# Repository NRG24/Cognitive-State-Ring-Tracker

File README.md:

# NERVA Ring

An open-source, sensor-packed smart ring designed to monitor cognitive health and autonomic nervous system metrics rather than traditional fitness tracking.

## Project Overview

The NERVA Ring shifts the focus of wearable technology away from step-counting and workouts toward real-time mental well-being. By embedding precise biosensors into a compact, flexible PCB form factor, the device continuously captures physiological indicators tied directly to stress, mental fatigue, and psychological arousal.

## Core Features

* **Cognitive Focus:** Tailored strictly for mental wellness monitoring rather than physical fitness or gym tracking.
* **Reviewed Hardware Design:** The v1 circuitry was modeled and validated in LT-Spice; the v2 netlist has been reviewed pin-by-pin against every device datasheet. No v2 board has been built or bench-validated yet.
* **Ultra-Compact Layout:** All hardware components optimized to fit onto a highly constrained, circular flex PCB architecture.
* **Wireless Telemetry:** Real-time, low-latency data streaming to mobile devices using Bluetooth Low Energy (BLE).
* **Intelligent Software Pipeline:** Dynamic in-app data filtering to remove motion artifacts and anomalies, powering a custom algorithm that delivers a "Cognitive Score" out of 100 alongside meaningful behavioral insights.

## Hardware Architecture

The current board is **NERVA Ring v2**, a complete part change from v1 — the MCU, both sensors, the op-amp, and the entire power path were replaced. Everything under `hardware/` and `firmware/` in this repo still describes the v1 board; see [Board Revisions](#board-revisions).

### Core components

| Role | Part | I²C address (7-bit) |
|------|------|---------------------|
| MCU / BLE | u-blox ANNA-B402-00B (nRF52833) | — |
| PPG (HR / SpO2) | MAXM86161 | `0x62` (`0xC4`/`0xC5` 8-bit) |
| IMU + die temperature | ST LSM6DSV | `0x6B` — SA0 tied to 1V8 |
| PMIC / charger / fuel gauge | TI BQ25120A | `0x6A` (fixed) |
| GSR analog front end | TI OPA2333 (dual op-amp) | — |
| LED boost converter | TI TPS61240 (fixed 5 V) | — |

All three I²C devices share a single bus. The IMU sits at **`0x6B`, not the ST default `0x6A`**: SA0 was originally grounded, which collided with the BQ25120A's fixed `0x6A`, so it was moved to the 1V8 rail.

### Pin map

**ANNA-B402 module pin numbers are not nRF GPIO numbers.** The `Pxx.yy` column is what firmware addresses.

There is **no UART and no USB** on this board — SWD is the only wired interface, so logging has to go over RTT rather than a serial port.

Because XL1/XL2 are grounded, the low-frequency clock has to come from the internal RC oscillator. There is no crystal to select.

### Power architecture

* **BQ25120A** is charger, buck regulator, and fuel gauge in one part. It supplies the SYS rail feeding the ANNA module, both sensors, and the analog front end. There is no separate LDO and no 3.3 V rail — the 3V3 rail was deleted, nothing uses it, and the PMIC's load switch / LDO output stays off (`LSCTRL`, ball E3, is tied to GND).
* **SYS runs at 1.9 V, not the 1.8 V default.** The default's −2.5 % corner is 1.755 V, which is below the OPA2333's 1.800 V minimum supply and only 55 mV above the ANNA's 1.70 V brown-out threshold. 1.9 V clears both, and costs nothing in GSR accuracy because the measurement is ratiometric — the rail cancels out.
* **The TS (thermistor) pin, ball C3, is physically unroutable on this layout and floats.** With TS sensing active the charger faults and delivers no current, so `TS_EN` has to be cleared before the cell will charge at all.
* Disabling TS also removes JEITA over-temperature protection from a lithium cell worn against skin, so charge-temperature limiting has to be reimplemented against the LSM6DSV die temperature and applied through the PMIC's `CE` bit.
* **Battery percentage comes from the BQ25120A's VBMON.** The v1 board had no fuel gauge at all.
* **TPS61240** generates the fixed 5 V VLED rail for the PPG, gated by `BOOST_EN`. It exists because of the green LED: VF is 3.0–3.8 V, against 2.1–2.5 V for red and 1.6–1.9 V for IR.
* Battery capacity (mAh) is still an open decision — it sets the fast-charge current and any honest runtime estimate.

### GSR front end

* Excitation is gated by `GSR_PWR` (P0.11, high drive) so the analog section can be powered down between samples, saving roughly 37 µA.
* Output lands on **AIN1 (P0.03)**. The SAADC is configured **reference VDD/4, gain 1/4**, so full scale equals VDD and the reading is ratiometric against the same rail that drives the excitation — supply drift cancels. The internal 0.6 V reference breaks that property.
* **40 µs acquisition time** is required by the 100 kΩ source impedance of R6.
* The C10/R6 filter has a ~100 ms time constant; allow ~300 ms after powering the front end before the first valid sample.
* Sampling must stay at **≥10 Hz** — skin-conductance responses peak ~1.4 s after onset, which is ~14 samples across the rise at 10 Hz but only ~3 at 2 Hz.
* Nominal conversion, 12-bit (0–4095): `G[µS] ≈ code × 0.009692 − 10.989`. Derived from nominal resistor values, so it needs trimming against a known resistance.

### PPG front end

* The MAXM86161 is powered **entirely from the 5 V VLED rail**. It is single-supply with an internal LDO, so taking `BOOST_EN` low unpowers the part completely and resets every register — a full re-init is required on each duty cycle.
* **Its interrupt pin is deliberately left unconnected**; the FIFO has to be polled.
* The I²C bus runs at 1.8 V and the MAXM86161 needs VIH ≥ 1.4 V, so no level shifter is required despite the 5 V VLED.
* **LED current range is a power-path constraint.** At the 124 mA range the boost pulls ~186 mA from the cell; on a small ring LiPo (~3 Ω internal resistance) that is ~560 mV of droop and starts crowding the BQ25120A's UVLO. The 31 mA range draws ~45 mA, about 135 mV of droop.

### IMU

* LSM6DSV at `0x6B`, with INT1 wired to P0.16.
* It is **not** an LSM6DS3 — different `WHO_AM_I` and different ODR / full-scale register encodings, so v1 register values do not carry the same meaning.
* Embedded temperature sensor at `OUT_TEMP_L/H` (0x20/0x21), 256 LSB/°C with 0 LSB = 25 °C. This is the die temperature used for the software charge-temperature limiting described above.

```
NERVA_Ring/
├── app/                        # Flutter mobile app ("GSR Streamer")
│   ├── lib/
│   │   ├── main.dart           # App entry point
│   │   ├── ble_service.dart    # BLE communication layer
│   │   ├── cognitive_scorer.dart
│   │   ├── gsr_analyzer.dart
│   │   ├── models/             # Data models
│   │   ├── screens/            # UI screens
│   │   ├── services/           # Business logic services
│   │   └── widgets/            # Reusable UI components
│   └── pubspec.yaml
├── firmware/                   # Arduino firmware sketches
│   ├── gsr_heart_ble/          # Main firmware + docs
│   │   ├── gsr_heart_ble.ino   # BLE biometric streaming (XIAO prototype)
│   │   └── *.ino              # Variant sketches (power-optimized, all-features, etc.)
│   ├── simple_ble/             # Minimal BLE test
│   └── *.ino                  # Standalone test sketches
├── hardware/                   # Hardware design files (v1 board)
│   ├── NERVA RING-bom.csv      # JLCPCB bill of materials (v1)
│   ├── BOM.md                  # Formatted BOM reference (v1)
│   ├── gsr_wearable.kicad_sch  # KiCad schematic
│   ├── gsr_wearable.kicad_pro  # KiCad project
│   ├── Ring CAD.step           # 3D CAD model
│   ├── pcb/                    # PCB layout files
│   ├── SCHEMATIC_CHECKLIST.md  # Design review checklist
│   ├── GSR_CIRCUIT_INTEGRATION.md
│   ├── PCB_LAYOUT_STRATEGY.md
│   └── *.md                   # Additional design docs
├── docs/                       # Software architecture docs
│   ├── ACTIVITY_RECOGNITION.md
│   ├── STRESS_PATTERN_ANALYSIS.md
│   ├── HAPTIC_NOTIFICATIONS.md
│   └── *.md
└── scripts/                    # Build/utility scripts
```

## Bill of Materials (Summary)

Active components on the **v2** board:

| Component | Part | Qty |
|-----------|------|-----|
| MCU / BLE module | ANNA-B402-00B (u-blox, nRF52833) | 1 |
| PPG sensor | MAXM86161 | 1 |
| IMU | LSM6DSV | 1 |
| PMIC / charger / fuel gauge | BQ25120A | 1 |
| GSR op-amp | OPA2333 (dual) | 1 |
| LED boost converter | TPS61240 (fixed 5 V) | 1 |
| Battery | Curved ring-type LiPo — capacity TBD | 1 |

> The BOM files in this repo — [`hardware/BOM.md`](hardware/BOM.md) and the raw JLCPCB export [`hardware/NERVA RING-bom.csv`](hardware/NERVA%20RING-bom.csv) — are the **v1** build, including passives, costs and LCSC part numbers. A v2 BOM has not been generated.

## Sensors & Data Streams

| Metric | Sensor (v2) | BLE UUID (suffix) | Type |
|--------|-------------|--------------------|------|
| GSR (Skin Conductance) | OPA2333 front end → SAADC AIN1 | `...0002` | Int |
| Heart Rate | MAXM86161 PPG | `...0003` | Int |
| Temperature | LSM6DSV die temp | `...0004` | Float |
| HRV (RMSSD) | Derived from PPG | `...0005` | Float |
| SpO2 | MAXM86161 PPG | `...0006` | Int |
| Battery Level | BQ25120A VBMON | `...0007` | Int |

**BLE Service UUID:** `19B10000-E8F2-537E-4F6C-D104768A1214`

The v2 IMU also makes raw accelerometer and gyroscope streams available. UUIDs and payload types above describe the app currently in `app/`; the BLE characteristic set is firmware/app scope and is not covered by this hardware pass.

## Board Revisions

Every design file in `hardware/` and every sketch in `firmware/` describes the **v1** board. v2 replaced all of it:

| Role | v1 | v2 (current) |
|------|----|--------------|
| MCU / BLE | Raytac MDBT42V (nRF52832) | u-blox ANNA-B402-00B (nRF52833) |
| PPG | MAX30102 | MAXM86161 |
| IMU | LSM6DSR (LSM6DSRTR) | LSM6DSV |
| GSR op-amp | LM324PWR (quad) | OPA2333 (dual) |
| Power | TLV70018DDCR 1.8 V LDO | BQ25120A PMIC (charger + buck + fuel gauge) |
| LED supply | — | TPS61240 fixed 5 V boost |
| Temperature source | MAX30102 die temp | LSM6DSV die temp |
| Battery monitoring | none | BQ25120A VBMON |

Consequences worth knowing:

* The KiCad project, Gerbers, BOM, and all layout/schematic notes under `hardware/` are v1 and have not been regenerated.
* v1 firmware does not port to v2. Beyond the sensor changes, the Adafruit nRF52 Arduino core supports nRF52832/nRF52840 only, while the ANNA-B402 is an nRF52833.

**Within the v1 documents themselves**, several files still reference even earlier parts: `SCHEMATIC_CHECKLIST.md`, `PCB_LAYOUT_STRATEGY.md`, and `GSR_CIRCUIT_INTEGRATION.md` mention LSM6DS3, TLV9004 (UQFN-14), and a 3.3 V MCP1700T-3302E LDO, and the JLCPCB BOM CSV lists MDBT50Q-1MV2 in the MCU slot rather than the MDBT42V actually fitted. `hardware/BOM.md` tracks that list. The firmware docs in `firmware/gsr_heart_ble/` describe the XIAO nRF52840 prototyping setup, not a ring board of either revision.

## Getting Started

### Mobile App
```bash
cd app
flutter pub get
flutter run
```

### Firmware (Prototype with XIAO nRF52840)
1. Install Arduino IDE with Seeed nRF52 board support
2. Install libraries: `ArduinoBLE`, `OneWire`, `DallasTemperature`
3. Wire sensors per `firmware/gsr_heart_ble/SETUP_INSTRUCTIONS.md`
4. Upload `firmware/gsr_heart_ble/gsr_complete_all_features.ino`

### Hardware
The KiCad project, Gerbers, and BOM in `hardware/` are the **v1** board: a 2-layer flex design with components on both sides, 0402/0201 passives, assembled by JLCPCB. v2 design files are not in this repo — the v2 description above comes from its netlist and datasheet review.

Bringing up a v2 board: attach a debug probe to SWD (module pins 41/42) and power it from a partially charged cell. **A fresh board will not charge on its own** — the floating TS pin holds the BQ25120A off until firmware clears `TS_EN`.

---

https://github.com/user-attachments/assets/21d7508c-1ee5-49b8-9717-f8bbbc1bc319

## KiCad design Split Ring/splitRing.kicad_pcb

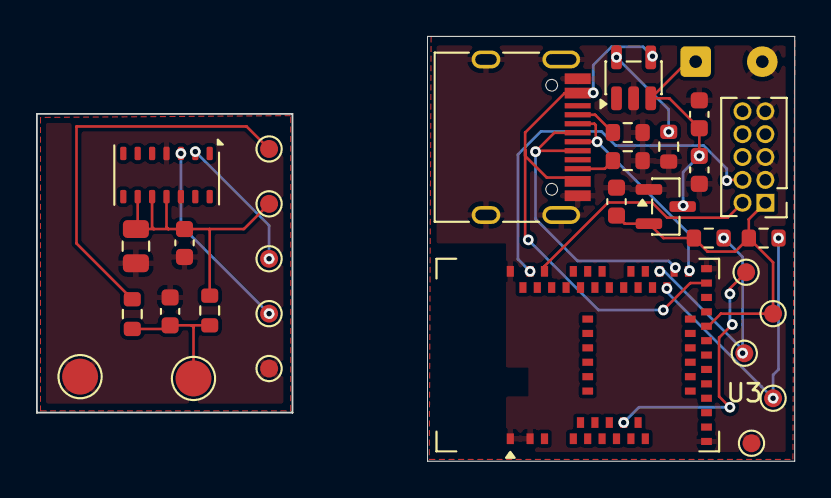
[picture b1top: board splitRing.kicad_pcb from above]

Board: 2 copper layers, 42.1 x 23.6 mm, 32 parts (0 on the bottom side), 15 nets.

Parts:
AGND1: TestPoint; TestPoint_Pad_D1.0mm
ASCL1: TestPoint; TestPoint_Pad_D1.0mm
ASDA1: TestPoint; TestPoint_Pad_D1.0mm
AVDD1: TestPoint; TestPoint_Pad_D1.0mm
A_GSR_ADC1: TestPoint; TestPoint_Pad_D1.0mm
BGND1: TestPoint; TestPoint_Pad_D1.0mm
BSCL1: TestPoint; TestPoint_Pad_D1.0mm
BSDA1: TestPoint; TestPoint_Pad_D1.0mm
BT1: Battery; SolderWire-0.127sqmm_1x02_P3.7mm_D0.48mm_OD1mm
BVDD1: TestPoint; TestPoint_Pad_D1.0mm
B_GSR_ADC1: TestPoint; TestPoint_Pad_D1.0mm
C1, C2: 10uF; C_0603_1608Metric
C5, C7: 1uF; C_0603_1608Metric
C6: 4.7uF; C_0805_2012Metric
C_GSR1: .1uF; C_0603_1608Metric
E1, E2: TestPoint; TestPoint_Pad_D2.0mm
J1: USB_C_Receptacle_USB2.0_16P; USB_C_Receptacle_HRO_TYPE-C-31-M-12
J2: SWD_HEADER; PinHeader_2x05_P1.27mm_Vertical
R1, R2: 4.7k; R_0603_1608Metric
R3: 30k; R_0603_1608Metric
R4, R5: 5.1k; R_0603_1608Metric
R_GSR1: 220k; R_0603_1608Metric
R_PROTECT1: 100k; R_0603_1608Metric
U1: MCP1700x-180xxTT; SOT-23
U2: MCP73831-2-OT; SOT-23-5
U3: MDBT50Q-1MV2; Raytac_MDBT50Q
U5: MAX30102; Maxim_OLGA-14_3.3x5.6mm_P0.8mm

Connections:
/D+: J1.A6 (D+), J1.B6 (D+), U3.35 (D+)
/D-: J1.A7 (D-), J1.B7 (D-), U3.34 (D-)
/GSR_ADC: A_GSR_ADC1.1, B_GSR_ADC1.1, R_PROTECT1.1, U3.11 (P0.02)
/GSR_SENSE: C_GSR1.1, E1.1, R_GSR1.1, R_PROTECT1.2
/SCL: ASCL1.1, BSCL1.1, R1.2, U3.37 (P0.13), U5.2 (SCL)
/SDA: ASDA1.1, BSDA1.1, R2.2, U3.36 (P0.14), U5.3 (SDA)
/SWDCLK: J2.4, U3.53 (SWDCLK)
/SWDIO: J2.2, U3.51 (SWDIO)
/VBAT: BT1.1 (+), C1.1, C7.1, U1.3 (VI), U2.3 (V_{BAT})
/VBUS: J1.A4 (VBUS), J1.A9 (VBUS), J1.B4 (VBUS), J1.B9 (VBUS), U2.4 (V_{DD}), U3.32 (VBUS)
/VDD: AVDD1.1, BVDD1.1, C2.2, C5.2, C6.2, J2.1, R1.1, R2.1, R_GSR1.2, U1.2 (VO), U3.28 (VDD), U5.9 (VLED+), U5.10 (VLED+), U5.11 (VDD)
GND: AGND1.1, BGND1.1, BT1.2 (-), C1.2, C2.1, C5.1, C6.1, C7.2, C_GSR1.2, E2.1, J1.A1 (GND), J1.A12 (GND), J1.B1 (GND), J1.B12 (GND), J1.S1 (SHIELD), J2.3, J2.5, J2.9, R3.2, R4.1, R5.1, U1.1 (GND), U2.2 (V_{SS}), U3.1 (GND), U3.2 (GND), U3.15 (GND), U3.33 (GND), U3.55 (GND), U5.4 (PGND), U5.12 (GND)
unnamed: J1.A5 (CC1), R4.2
unnamed: J1.B5 (CC2), R5.2
unnamed: R3.1, U2.5 (PROG)

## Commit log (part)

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2025-12-06 Update README with project status
2025-12-12 Easy access to PCB
2025-12-12 Update README with PCB estimate and BOM details
    Added PCB cost estimate and BOM link to README.
2025-12-12 Add image to README for visual reference
2025-12-12 Update README with project details and PCB estimate
    Added information about project resources and PCB cost estimate.
2025-12-13 Clean up README by removing outdated information
    Removed update section and Bill of Materials link from README.
2026-01-06 CAD FILE
2026-01-25 Revise README to enhance project description
    Updated the README to include an accelerometer and emphasize the focus on cognitive health. Added details about testing circuitry in LT-Spice.
2026-01-26 Add new screenshot to README
2026-01-26 Update README with project details and images
    Removed a sentence about project contents and added images.
2026-01-26 Update README with flex PCB details
    Added additional context regarding the flex PCB and its components.
2026-02-08 Add image to README for project illustration
    Added an additional image to the README to illustrate the project.
2026-02-08 Fix duplicate image in README
    Removed duplicate image entry in the README.
2026-02-12 Update images in README.md
    Added new screenshots and removed some outdated ones.
2026-02-12 Update screenshots in README.md
    Removed an outdated screenshot and added a new one.
2026-03-22 Update images in README.md
    Removed several old screenshots and added new ones to better represent the project.
2026-04-08 Add nRF52832 RPi Debug Probe programming guide with README and openocd.cfg
    Agent-Logs-Url: https://github.com/NRG24/Cognitive-State-Ring-Tracker/sessions/17d30383-7a80-4812-84ac-a320171a4d4e
2026-04-08 Repo restructure: hardware/pcb, arduino/xiao, app/other; moved sketches and PCB files
2026-04-08 chore: reorganize repo into 5 folders (docs, firmware, hardware, scripts, app)
    Agent-Logs-Url: https://github.com/NRG24/Cognitive-State-Ring-Tracker/sessions/de9945f7-d82a-4161-8b5d-edef97d8b796
2026-04-08 update app display name and add RUNNING_GUIDE.md
    Agent-Logs-Url: https://github.com/NRG24/Cognitive-State-Ring-Tracker/sessions/44975d6f-7a5f-45c4-9d12-b31ac7f7ca64
2026-04-08 Fix nRF52 flash scripts, update Info.plist BT permissions, add scripts/README
2026-04-28 Add project overview to README
    Added introductory text about the project and its focus on cognitive health.
2026-04-28 Clear esp32_mp3_spotify.ino file
    Remove all existing code and comments from esp32_mp3_spotify.ino.
